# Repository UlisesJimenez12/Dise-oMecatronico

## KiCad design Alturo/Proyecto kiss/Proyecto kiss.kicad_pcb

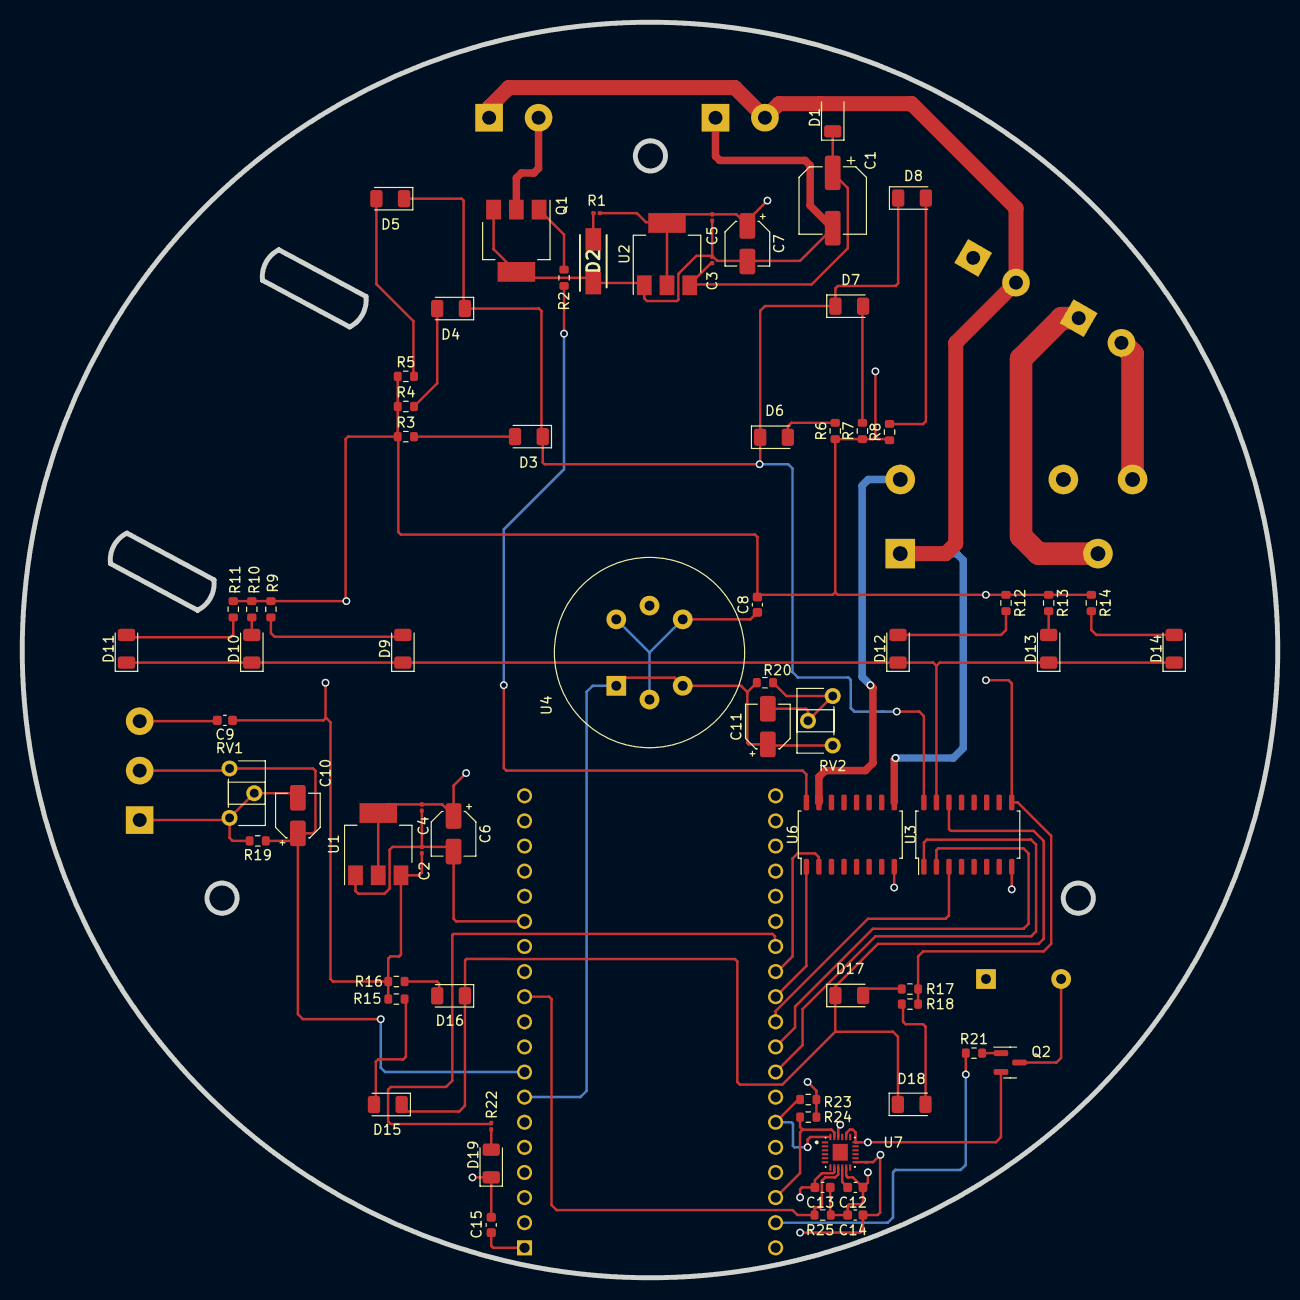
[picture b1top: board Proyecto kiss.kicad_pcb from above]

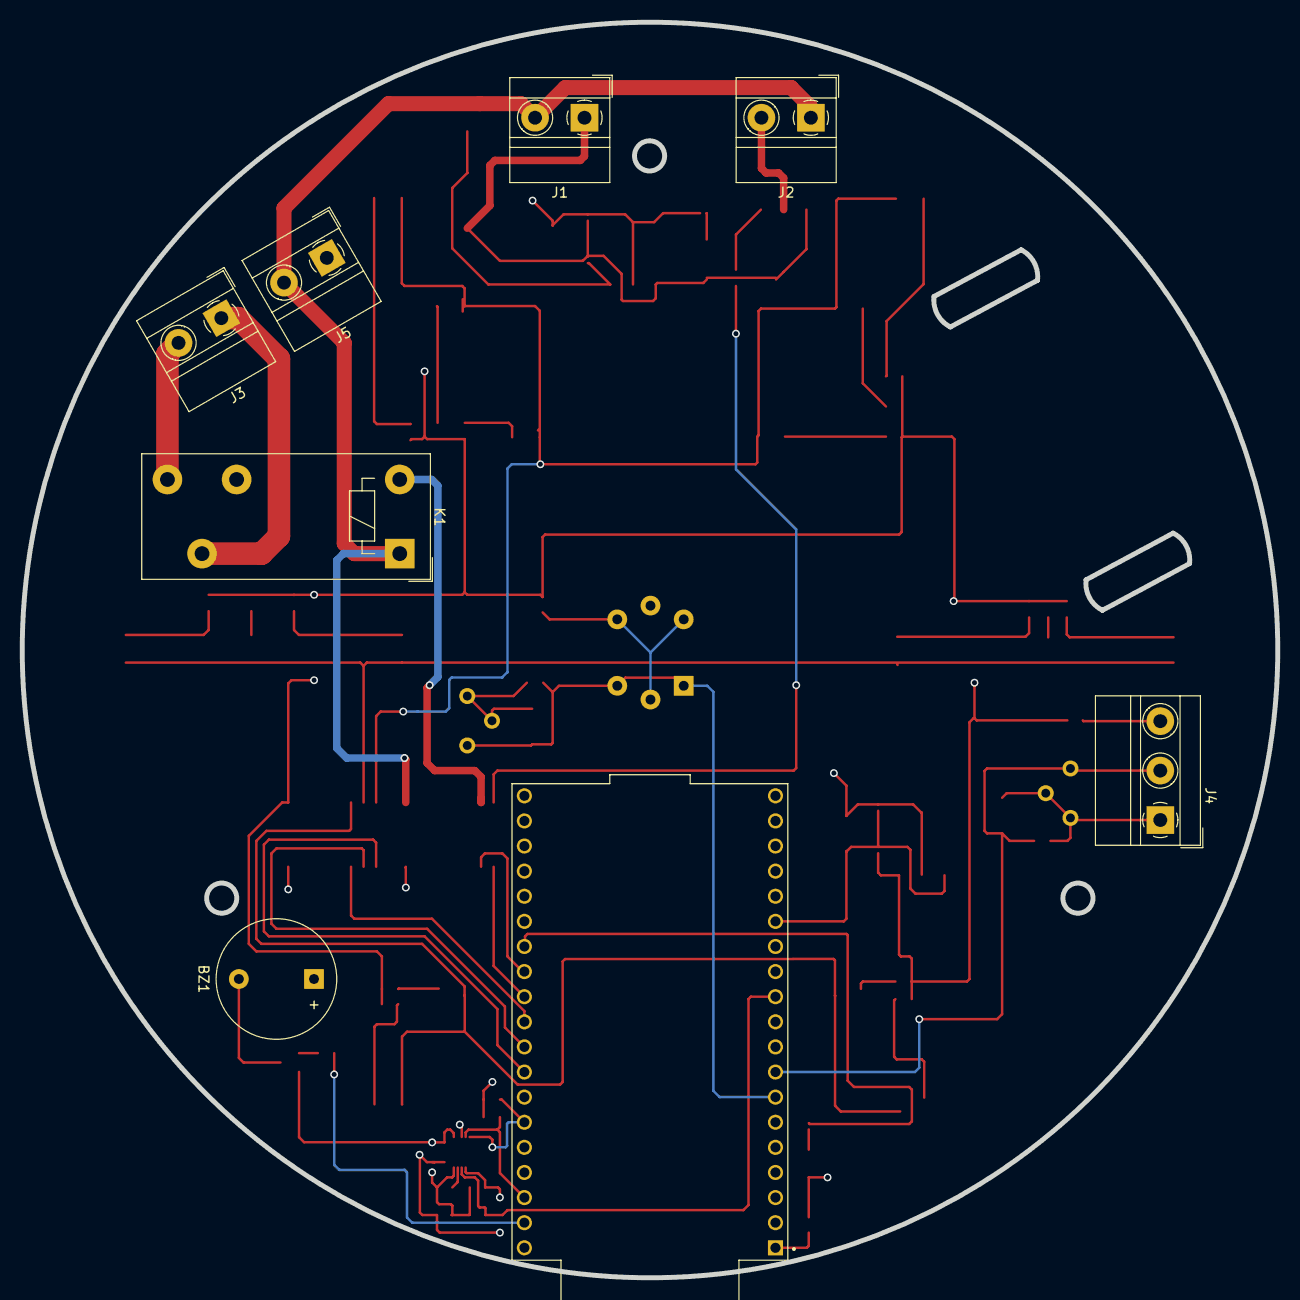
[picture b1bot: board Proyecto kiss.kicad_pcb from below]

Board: 4 copper layers, 127.0 x 127.0 mm, 77 parts (8 on the bottom side), 49 nets.

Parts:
BZ1: Buzzer; Buzzer_12x9.5RM7.6
C1: 100uf; CP_Elec_6.3x5.4
C2, C3, C4, C5: 100nf; C_0201_0603Metric
C6, C7: 22uf; CP_Elec_4x5.4
C8, C9, C12, C14, C15: 100nf; C_0603_1608Metric
C10, C11: 4.7 uF; CP_Elec_4x5.4
C13: 10nF; C_0603_1608Metric
D1: M7; LED_1206_3216Metric
D2: Green_Led; DIOM5327X240N
D3, D4, D5, D6, D7, D8: Red_Led; LED_1206_3216Metric
D9, D10, D11, D12, D13, D14: Blue_Led; LED_1206_3216Metric
D15, D16, D17, D18: Yellow_Led; LED_1206_3216Metric
D19: Green_Led; LED_1206_3216Metric
J1, J2, J3, J5: TB2; TerminalBlock_MetzConnect_Type011_RT05502HBWC_1x02_P5.00mm_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
J4: TB3; TerminalBlock_MetzConnect_Type011_RT05503HBWC_1x03_P5.00mm_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
K1: FINDER-40.31; Relay_SPDT_Finder_40.31
Q1: BSP75N; SOT-223
Q2: BC817; SOT-23
R1, R22: 220; R_0201_0603Metric
R2, R3, R4, R5, R6, R7, R8, R9, R10, R11, R12, R13, R14, R15, R16, R17, R18: 220; R_0603_1608Metric
R19, R20: 100; R_0603_1608Metric
R21: 1K; R_0603_1608Metric
R23, R24, R25: 10k; R_0603_1608Metric
RV1, RV2: 20K; Potentiometer_ACP_CA6-H2,5_Horizontal
U1: AMS1117-3.3; SOT-223-3_TabPin2
U2: AMS1117-5.0; SOT-223-3_TabPin2
U3, U6: ULN2003; SOIC-16_4.55x10.3mm_P1.27mm
U4: MQ-6
U5: ESP32-DEVKITC; MODULE_ESP32-DEVKITC
U7: MPU-6500; QFN40P300X300X95-25N

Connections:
+3.3V: BZ1.1 (-), C4.1, C6.1, C13.2, C14.2, C15.1, U1.2 (VO), U5.1 (3V3), U7.8 (VDDIO), U7.13 (VDD), U7.22 (NCS)
+5V: C2.1, C5.1, C7.1, C8.2, C9.1, R1.1, R3.1, R4.1, R5.1, R6.1, R7.1, R8.1, R9.1, R10.1, R11.1, R12.1, R13.1, R14.1, R15.1, R16.1, R17.1, R18.1, U1.3 (VI), U2.2 (VO), U3.9 (COM)
+12V: D1.2, J1.2, J2.1, J5.2, K1.A1, U6.9 (COM)
/Mod_ESP32/Db_led: R22.1, U5.26 (IO4)
/Mod_Relay/Com: J3.1, K1.11
/Mod_Relay/NO: J3.2, K1.14
/Mod_trans/Trans_out: J2.2, Q1.2 (D)
/Pin_MPU: R25.1, U5.11 (IO27), U7.9 (AD0/SDO)
/Pin_RL: K1.A2, U6.15 (O2)
/Pin_bzz: R21.1, U5.37 (IO23)
/Pin_trans: R2.1, U6.16 (O1)
/SCL: R24.1, U5.36 (IO22), U7.23 (SCL/SCLK)
/SDA: R23.1, U5.33 (IO21), U7.24 (SDA/SDI)
/Sen_ext: C10.1, J4.2, R19.1, RV1.1, U5.8 (IO33)
/Sen_int: C11.1, R20.1, RV2.1, U4.1 (B1), U4.3 (B2), U5.7 (IO32)
/ledB: U3.2 (I2), U5.30 (IO18)
/ledR: U3.1 (I1), U5.31 (IO19)
/ledY: U3.3 (I3), U5.29 (IO5)
Earth: C1.2, C2.2, C3.2, C4.2, C5.2, C6.2, C7.2, C10.2, C11.2, C12.2, C13.1, C14.1, C15.2, D2.1 (K), D19.1 (K), J1.1, J4.1, J5.1, Q1.3 (S), Q1.4 (S), Q2.2 (E), R19.2, R20.2, R23.2, R24.2, R25.2, RV1.2, RV1.3, RV2.2, RV2.3, U1.1 (GND), U2.1 (GND), U3.8 (GND), U4.5 (VH-), U5.14 (GND1), U6.8 (GND), U7.11 (FSYNC), U7.18 (GND), U7.20 (RESV_2)
unnamed: BZ1.2 (+), Q2.3 (C)
unnamed: D2.2 (A), R1.2
unnamed: D3.2 (A), R3.2
unnamed: D3.1 (K), D4.1 (K), D5.1 (K), D6.1 (K), D7.1 (K), D8.1 (K), U3.16 (O1)
unnamed: D4.2 (A), R4.2
unnamed: D5.2 (A), R5.2
unnamed: D6.2 (A), R6.2
unnamed: D7.2 (A), R7.2
unnamed: D8.2 (A), R8.2
unnamed: D9.2 (A), R9.2
unnamed: D10.2 (A), R10.2
unnamed: D9.1 (K), D10.1 (K), D11.1 (K), D12.1 (K), D13.1 (K), D14.1 (K), U3.15 (O2)
unnamed: D11.2 (A), R11.2
unnamed: D12.2 (A), R12.2
unnamed: D13.2 (A), R13.2
unnamed: D14.2 (A), R14.2
unnamed: D15.2 (A), R15.2
unnamed: D15.1 (K), D16.1 (K), D17.1 (K), D18.1 (K), U3.14 (O3)
unnamed: D16.2 (A), R16.2
unnamed: D17.2 (A), R17.2
unnamed: D18.2 (A), R18.2
unnamed: D19.2 (A), R22.2
unnamed: C9.2, J4.3
unnamed: Q1.1 (G), R2.2
unnamed: Q2.1 (B), R21.2
unnamed: C1.1, C3.1, D1.1, U2.3 (VI)
unnamed: C8.1, U4.2 (VH+), U4.4 (A2), U4.6 (A1)
unnamed: U5.27 (IO16), U6.2 (I2)
unnamed: U5.28 (IO17), U6.1 (I1)
unnamed: C12.1, U7.10 (REGOUT)

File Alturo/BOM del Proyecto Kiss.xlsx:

Reference | Value | Footprint | Datasheet | Manufacturer_Part_Number | Mouser Price/Stock | Cdad
BZ1 | Buzzer | Buzzer_Beeper:Buzzer_12x9.5RM7.6 | https://www.mouser.com/datasheet/2/683/IE122303-1-358179.pdf | IE122303-1 | https://www.mouser.com/ProductDetail/DB-Unlimited/IE122303-1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 | 1
C1 | 100uf | Capacitor_SMD:CP_Elec_6.3x5.4 | https://www.mouser.com/datasheet/2/88/AVS-3081846.pdf | AVS107M16D16T-F | https://www.mouser.com/ProductDetail/Cornell-Dubilier-CDE/AV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 | 1
C2-C5, C8, C9, C12, C14, C15 | 100nf | -- valores mixtos -- | https://www.mouser.com/datasheet/2/212/KEM_C1023_X7R_AUTO_SM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 | C0603C104K5RAC3121 | https://www.mouser.com/ProductDetail/KEMET/C0603C104K5RAC312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 | 9
C6, C7 | 22uf | Capacitor_SMD:CP_Elec_4x5.4 | https://www.mouser.com/datasheet/2/212/KEM_A4049_EDH-1102962.pdf | EDH226M016S9BAA | https://www.mouser.com/ProductDetail/KEMET/EDH226M016S9BAA?q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 | 2
C10, C11 | 4.7 uF | Capacitor_SMD:CP_Elec_4x5.4 | https://www.mouser.com/datasheet/2/315/AAB8000C193-947353.pdf | 10SVP4R7M | https://www.mouser.com/ProductDetail/Panasonic/10SVP4R7M?qs=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 | 2
C13 | 10nF | Capacitor_SMD:C_0603_1608Metric | https://www.mouser.com/datasheet/2/396/Taiyo_Yuden_19_MAASL0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 | MAASL063SB7103MFCA01 | https://www.mouser.com/ProductDetail/TAIYO-YUDEN/MAASL063SB7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 | 1
D1 | M7 | M7:DIOM5327X240N | https://www.mouser.in/datasheet/2/849/m1-2577421.pdf | M7 | https://www.mouser.co.uk/ProductDetail/Diotec-Semiconductor/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 | 1
D2 | Green_Led | LED_SMD:LED_1206_3216Metric | https://www.rohm.com/datasheet?p=SML-S13PT&dist=Mouser&media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 | SML-S13PTT68 | https://www.mouser.com/ProductDetail/ROHM-Semiconductor/SML-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 | 1
D3-D8 | Red_Led | LED_SMD:LED_1206_3216Metric | https://www.rohm.com/datasheet?p=SML-S13UT&dist=Mouser&media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 | SML-S13UTT68 | https://www.mouser.com/ProductDetail/ROHM-Semiconductor/SML-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 | 6
D9-D14 | Blue_Led | LED_SMD:LED_1206_3216Metric | https://www.mouser.com/datasheet/2/678/AV02_0977EN_2020_10_2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 | HSMR-C150 | https://www.mouser.com/ProductDetail/Broadcom-Avago/HSMR-C15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 | 6
D15-D18 | Yellow_Led | LED_SMD:LED_1206_3216Metric | https://www.rohm.com/datasheet?p=SML-S13YT&dist=Mouser&media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 | SML-S13YTT68 | https://www.mouser.com/ProductDetail/ROHM-Semiconductor/SML-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 | 4
J1-J3, J5 | TB2 | TerminalBlock_MetzConnect:TerminalBlock_MetzConnect_Type011_RT05502HBWC_1x02_P5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 | https://www.mouser.com/datasheet/2/670/tb002_500-2306853.pdf | TB002-500-02BE | https://www.mouser.com/ProductDetail/CUI-Devices/TB002-500-0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 | 4
J4 | TB3 | TerminalBlock_MetzConnect:TerminalBlock_MetzConnect_Type011_RT05503HBWC_1x03_P5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 | https://www.mouser.com/ProductDetail/Wurth-Elektronik/691101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 | 691101710003 | https://www.mouser.com/datasheet/2/445/691101710003-3089887.pdf | 1
K1 | FINDER-40.31 | Relay_THT:Relay_SPDT_Finder_40.31 | http://gfinder.findernet.com/assets/Series/353/S40EN.pdf | 40.31.8.230.0000 | https://us.rs-online.com/product/finder/40-31-8-230-0000/70747659/ | 1
Q1 | BSP75N | Package_TO_SOT_SMD:SOT-223 | https://www.infineon.com/dgdl/Infineon-BSP75N-DS-v01_04-en.p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 | BSP75N | https://www.mouser.com/ProductDetail/Infineon-Technologies/B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 | 1
Q2 | BC817 | Package_TO_SOT_SMD:SOT-23 | https://www.mouser.com/datasheet/2/345/bc817-2449263.pdf | BC817 | https://www.mouser.com/ProductDetail/Rectron/BC817?qs=sGAEpi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 | 1
R1-R18 | 220 | -- valores mixtos -- | https://www.mouser.com/datasheet/2/427/crcw0201e3-1761851.pdf | CRCW0201220KFKED | https://www.mouser.com/ProductDetail/Vishay-Dale/CRCW0201220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 | 18
R19, R20 | 100 | Resistor_SMD:R_0603_1608Metric | https://www.mouser.com/datasheet/2/315/PANA_S_A0013004771_1-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 | ERA-1AEB101C | https://www.mouser.com/ProductDetail/Panasonic/ERA-1AEB101C?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 | 2
R21 | 1K | Resistor_SMD:R_0603_1608Metric | https://www.mouser.com/datasheet/2/418/8/ENG_DS_1773200_N2-2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 | CPF0201B1K0E1 | https://www.mouser.com/ProductDetail/TE-Connectivity-Holswor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 | 1
RV1, RV2 | 20K | Potentiometer_THT:Potentiometer_ACP_CA6-H2,5_Horizontal | https://www.mouser.com/datasheet/2/670/ptn06-3075547.pdf | PTN06-B20CC20 | https://www.mouser.com/ProductDetail/CUI-Devices/PTN06-B20CC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 | 2
U1 | AMS1117-3.3 | Package_TO_SOT_SMD:SOT-223-3_TabPin2 | https://www.ti.com/general/docs/suppproductinfo.tsp?distId=2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 | REG1117-3.3 | https://www.mouser.com/ProductDetail/Texas-Instruments/REG11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 | 1
U2 | AMS1117-5.0 | Package_TO_SOT_SMD:SOT-223-3_TabPin2 | https://www.ti.com/general/docs/suppproductinfo.tsp?distId=2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 | REG1117-5 | https://www.mouser.com/ProductDetail/Texas-Instruments/REG11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 | 1
U3, U6 | ULN2003 | Package_SO:SOIC-16_4.55x10.3mm_P1.27mm | http://www.ti.com/lit/ds/symlink/uln2003a.pdf | ULN2004AD | https://www.mouser.com/ProductDetail/Texas-Instruments/ULN20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 | 2
U4 | MQ-6 | Sensor:MQ-6 | https://www.winsen-sensor.com/d/files/semiconductor/mq-6.pdf | MQ-6 | https://www.ebay.com/itm/191834810651?hash=item2caa3ee91b:g: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 | 1
U5 | ESP32-DEVKITC | esp32:MODULE_ESP32-DEVKITC | https://esp-idf.readthedocs.io/en/latest/get-started/get-sta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 | ESP32-DevKitC | https://www.mouser.com/ProductDetail/Espressif-Systems/ESP32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 | 1
U7 | MPU-6500 | MPU-6500:QFN40P300X300X95-25N | https://product.tdk.com/system/files/dam/doc/product/sensor/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 | MPU-6500 | https://www.mouser.com/ProductDetail/TDK-InvenSense/MPU-6500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 | 1

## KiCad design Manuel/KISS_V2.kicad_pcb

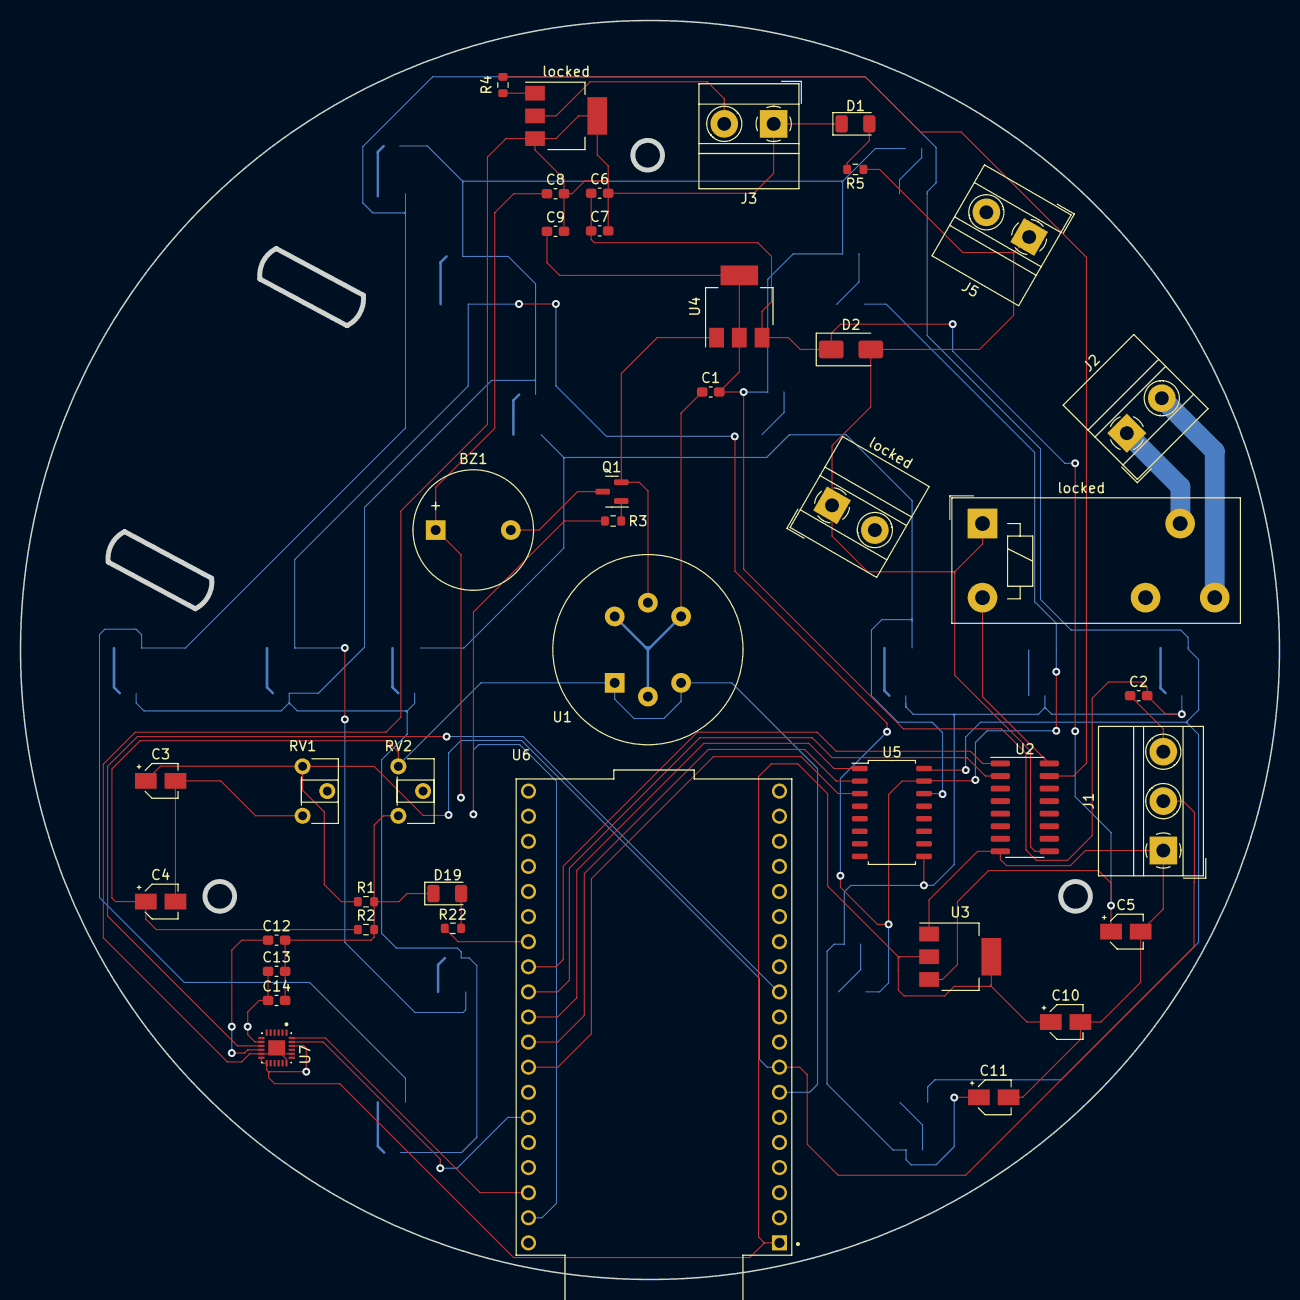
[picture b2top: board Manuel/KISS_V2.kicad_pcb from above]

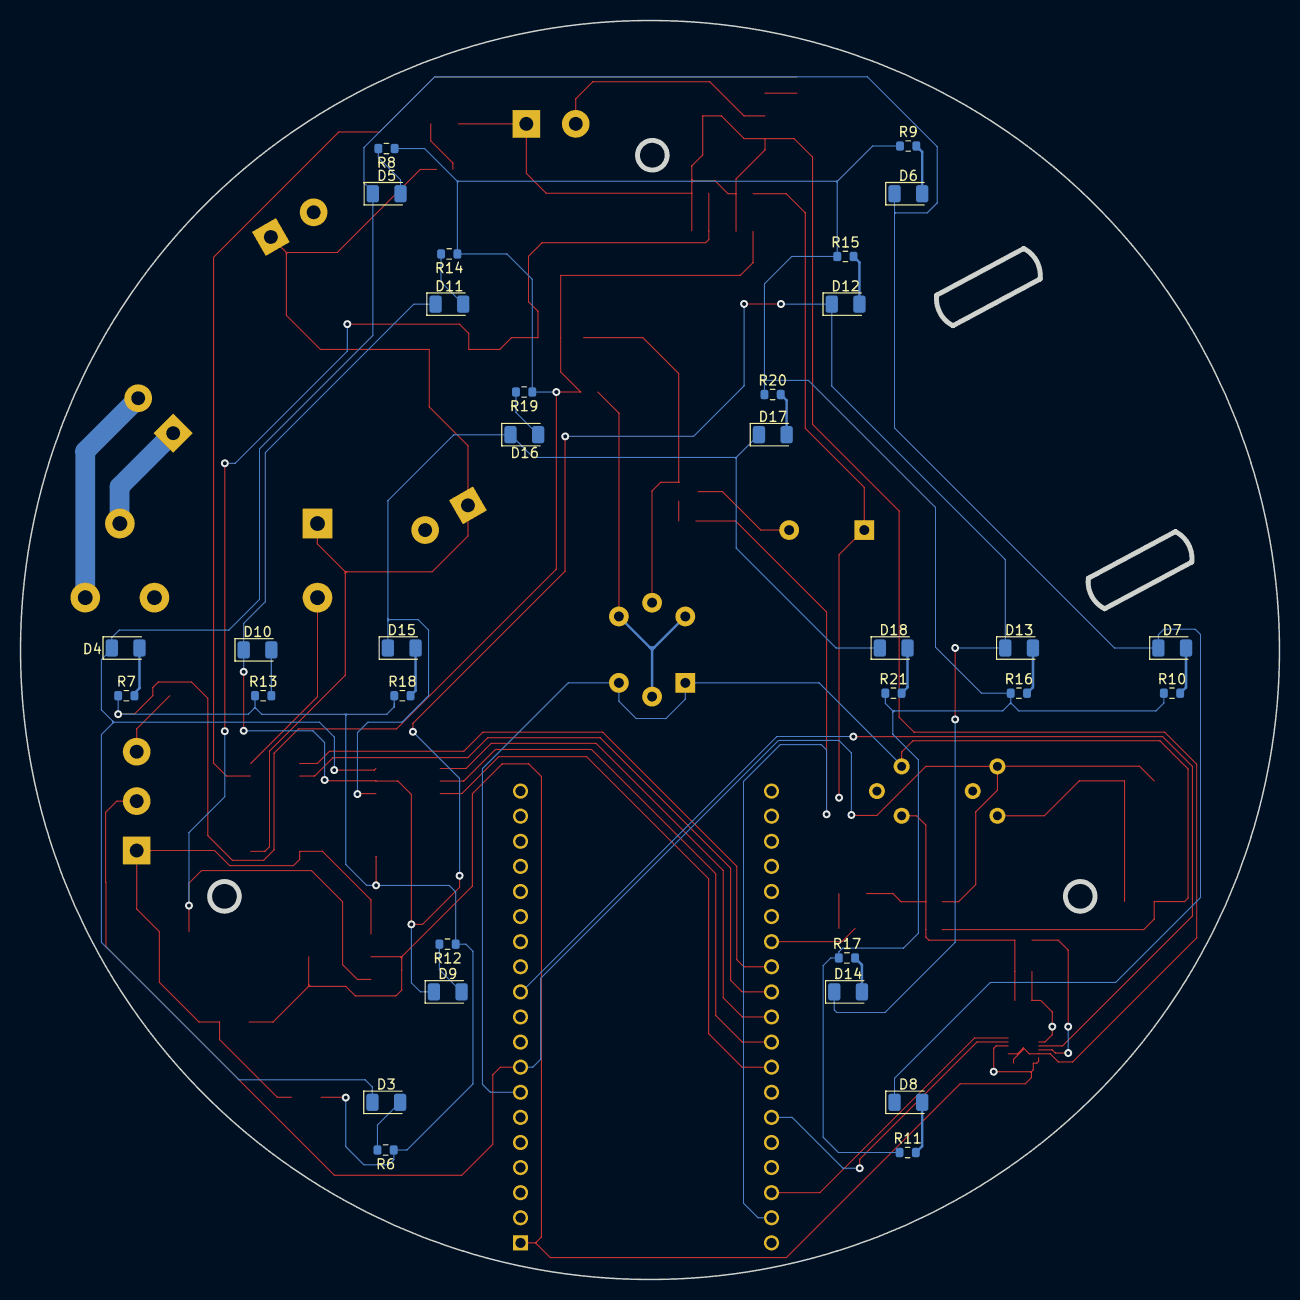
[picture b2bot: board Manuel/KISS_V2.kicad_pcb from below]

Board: 4 copper layers, 127.4 x 127.4 mm, 73 parts (32 on the bottom side), 49 nets.

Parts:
BZ1: Buzzer; Buzzer_12x9.5RM7.6
C1, C2: 100nF; C_0603_1608Metric_Pad1.08x0.95mm_HandSolder
C3, C4: 4.7 uF; CP_Elec_3x5.3
C5: 100uf; CP_Elec_3x5.3
C6, C7, C8, C9: 100nf; C_0603_1608Metric_Pad1.08x0.95mm_HandSolder
C10, C11: 22uf; CP_Elec_3x5.3
C12, C14: 0.1μF; C_0603_1608Metric_Pad1.08x0.95mm_HandSolder
C13: 10nF; C_0603_1608Metric_Pad1.08x0.95mm_HandSolder
D1, D3, D4, D5, D7, D8, D9, D10, D11, D12, D13, D14, D15, D16, D17, D18, D19: LED; LED_1206_3216Metric
D2: M1; D_SMA
D6: locked; LED_1206_3216Metric
J1: Screw_Terminal_01x03; TerminalBlock_MetzConnect_Type011_RT05503HBWC_1x03_P5.00mm_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
J2, J3, J5: Screw_Terminal_01x02; TerminalBlock_MetzConnect_Type011_RT05502HBWC_1x02_P5.00mm_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
Q1: BC817; SOT-23
R1, R2: 100; R_0603_1608Metric
R3: 1K; R_0603_1608Metric
R4, R5, R6, R7, R8, R9, R10, R11, R12, R13, R14, R15, R16, R17, R18, R19, R20, R21, R22: 220; R_0603_1608Metric
RV1, RV2: 20K; Potentiometer_ACP_CA6-H2,5_Horizontal
U1: MQ-6
U2: ULN2003; SOIC-16_3.9x9.9mm_P1.27mm
U3: AMS1117-3.3; SOT-223-3_TabPin2
U4: AMS1117-5.0; SOT-223-3_TabPin2
U5: ULN2003; SOIC-16_4.55x10.3mm_P1.27mm
U6: ESP32-DEVKITC; MODULE_ESP32-DEVKITC
U7: MPU-6500; QFN40P300X300X95-25N
locked: Screw_Terminal_01x02; TerminalBlock_MetzConnect_Type011_RT05502HBWC_1x02_P5.00mm_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
locked#2: locked; SOT-223
locked#3: locked; Relay_SPDT_Finder_40.31

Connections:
3.3V: BZ1.1 (-), C8.1, C10.1, C13.1, C14.1, U3.2 (VO), U6.1 (3V3), U7.8 (VDDIO), U7.12 (INT), U7.13 (VDD), U7.22 (NCS)
5V: C1.2, C2.1, C9.1, C11.1, R6.1, R7.1, R8.1, R9.1, R10.1, R11.1, R12.1, R13.1, R14.1, R15.1, R16.1, R17.1, R18.1, R19.1, R20.1, R21.1, U4.2 (VO), U5.9 (COM)
/Buzzer/Activador del buzzer: R3.1, U6.37 (IO23)
/Controlador/COM: J2.1, locked#3.11
/Controlador/Modulo de Diodos/D1: U2.16 (O1), locked#3.A2
/Controlador/Modulo de Diodos/EN_D1: U2.1 (I1), U6.27 (IO16)
/Controlador/Modulo de Diodos/EN_D2: U2.2 (I2), U6.28 (IO17)
/Controlador/NA_RL: J2.2, locked#3.14
/Controlador/Pin_Activador_LEDam: U5.1 (I1), U6.29 (IO5)
/Controlador/Pin_Activador_LEDaz: U5.2 (I2), U6.30 (IO18)
/Controlador/Pin_Activador_LEDr: U5.3 (I3), U6.31 (IO19)
/Controlador/Pin_Sensor_Gas: C4.1, R2.1, RV2.1, U1.1 (B1), U1.3 (B2), U6.7 (IO32)
/Controlador/Pin_Sensor_GasEx: C3.1, J1.2, R1.1, RV1.1, U6.8 (IO33)
/Controlador/SALIDA TRANSISTOR: J3.2, locked#2.2 (D)
/Controlador/SCL: U6.36 (IO22), U7.24 (SDA/SDI)
/Controlador/SDA: U6.33 (IO21), U7.23 (SCL/SCLK)
/Controlador/Salida_Giroscopio: U6.11 (IO27), U7.9 (AD0/SDO)
Activador de transistor: R4.1, U2.15 (O2)
Earth: C3.2, C4.2, C5.2, C6.2, C7.2, C8.2, C9.2, C10.2, C11.2, C12.2, C13.2, C14.2, D1.1 (K), D19.1 (K), J1.1, J3.1, J5.2, Q1.2 (E), R1.2, R2.2, RV1.2, RV1.3, RV2.2, RV2.3, U1.5 (VH-), U2.8 (GND), U3.1 (GND), U4.1 (GND), U6.14 (GND1), U7.11 (FSYNC), U7.18 (GND), U7.20 (RESV_2), U7.25 (EXP), locked.2, locked#2.3 (S), locked#2.4 (S)
unnamed: BZ1.2 (+), Q1.3 (C)
unnamed: D1.2 (A), R5.2
unnamed: C5.1, C6.1, C7.1, D2.1 (K), U3.3 (VI), U4.3 (VI)
unnamed: D3.2 (A), R6.2
unnamed: D3.1 (K), D4.1 (K), D5.1 (K), D6.1 (K), D7.1 (K), D8.1 (K), U5.16 (O1)
unnamed: D4.2 (A), R7.2
unnamed: D5.2 (A), R8.2
unnamed: D6.2 (A), R9.2
unnamed: D7.2 (A), R10.2
unnamed: D8.2 (A), R11.2
unnamed: D9.2 (A), R12.2
unnamed: D10.2 (A), R13.2
unnamed: D9.1 (K), D10.1 (K), D11.1 (K), D12.1 (K), D13.1 (K), D14.1 (K), U5.15 (O2)
unnamed: D11.2 (A), R14.2
unnamed: D12.2 (A), R15.2
unnamed: D13.2 (A), R16.2
unnamed: D14.2 (A), R17.2
unnamed: D15.2 (A), R18.2
unnamed: D15.1 (K), D16.1 (K), D17.1 (K), D18.1 (K), U5.14 (O3)
unnamed: D16.2 (A), R19.2
unnamed: D17.2 (A), R20.2
unnamed: D18.2 (A), R21.2
unnamed: D19.2 (A), R22.2
unnamed: C2.2, J1.3
unnamed: Q1.1 (B), R3.2
unnamed: R4.2, locked#2.1 (G)
unnamed: C1.1, U1.2 (VH+), U1.4 (A2), U1.6 (A1)
unnamed: R22.1, U6.26 (IO4)
unnamed: C12.1, U7.10 (REGOUT)
Positivo de bateria: D2.2 (A), J5.1, R5.1, U2.9 (COM), locked.1, locked#3.A1

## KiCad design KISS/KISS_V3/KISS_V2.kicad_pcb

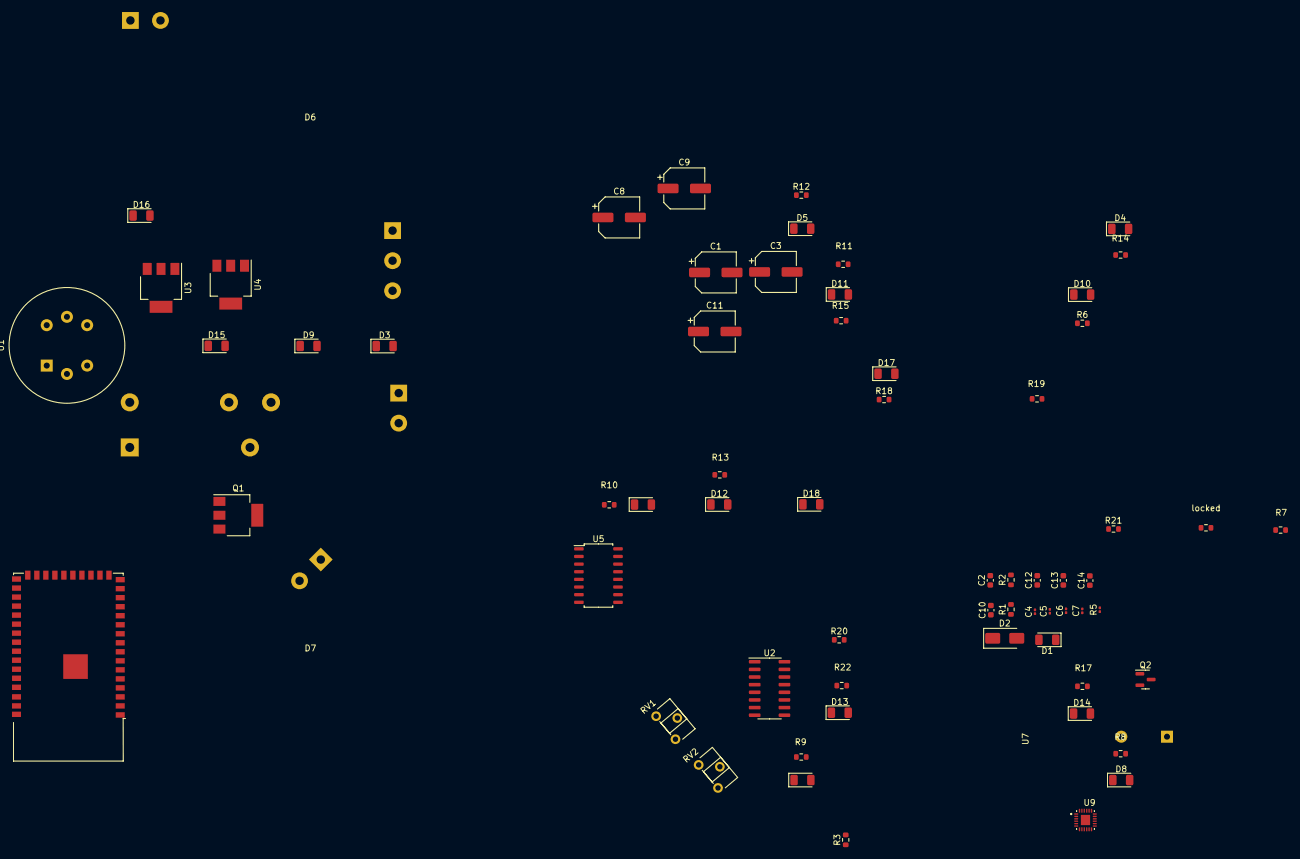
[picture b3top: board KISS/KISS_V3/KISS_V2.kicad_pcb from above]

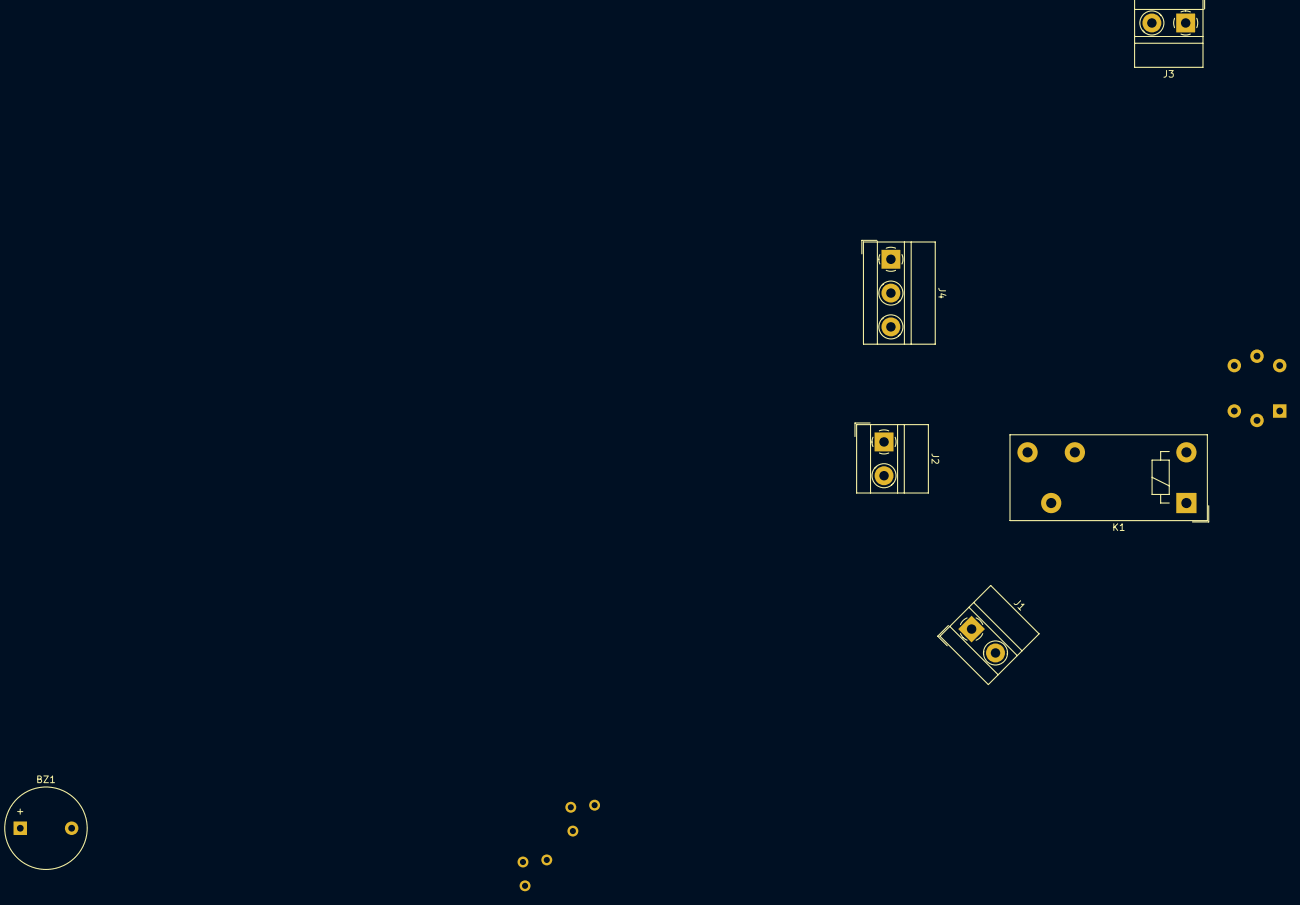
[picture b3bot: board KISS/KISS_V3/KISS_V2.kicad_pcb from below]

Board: 2 copper layers, 70 parts (6 on the bottom side), 48 nets, no tracks yet.

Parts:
BZ1: Buzzer; Buzzer_12x9.5RM7.6
C1, C11: 4.7 uF; CP_Elec_6.3x7.7
C2, C10: C; C_0603_1608Metric
C3: 100uf; CP_Elec_6.3x3
C4, C5, C6, C7: 100nf; C_0201_0603Metric
C8, C9: 22uf; CP_Elec_6.3x3
C12, C13: 0.1μF; C_0603_1608Metric
C14: 10nF; C_0603_1608Metric
D1, D3, D4, D5, D6, D7, D8, D9, D10, D11, D12, D13, D14, D15, D16, D17, D18: LED; LED_1206_3216Metric
D2: M1; D_SMA
J1, J2, J3: Screw_Terminal_01x02; TerminalBlock_MetzConnect_Type011_RT05502HBWC_1x02_P5.00mm_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
J4: Screw_Terminal_01x03; TerminalBlock_MetzConnect_Type011_RT05503HBWC_1x03_P5.00mm_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
K1: FINDER-40.31; Relay_SPDT_Finder_40.31
Q1: BSP75N; SOT-223
Q2: BC817; SOT-23
R1, R2: 100; R_0603_1608Metric
R3: 1K; R_0603_1608Metric
R5: 220; R_0201_0603Metric
R6, R7, R8, R9, R10, R11, R12, R13, R14, R15, R17, R18, R19, R20, R21, R22: 220; R_0603_1608Metric
RV1, RV2: 60K; Potentiometer_ACP_CA6-H2,5_Horizontal
U1: MQ-6
U2: ULN2003; SOIC-16_3.9x9.9mm_P1.27mm
U3: AMS1117-3.3; SOT-223-3_TabPin2
U4: AMS1117-5.0; SOT-223-3_TabPin2
U5: ULN2003; SOIC-16_4.55x10.3mm_P1.27mm
U7: ESP32-S2-WROVER-I; ESP32-S2-WROVER
U9: MPU-6500; QFN40P300X300X95-25N
locked: 220; R_0603_1608Metric

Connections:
3.3V: BZ1.1 (-), C6.1, C8.1, C12.2, C14.2, U3.2 (VO), U7.2 (3V3), U9.8 (VDDIO), U9.12 (INT), U9.13 (VDD), U9.22 (NCS)
5V: C2.2, C7.1, C9.1, C10.1, R6.1, R7.1, R8.1, R9.1, R10.1, R11.1, R12.1, R13.1, R14.1, R15.1, R17.1, R18.1, R19.1, R21.1, R22.1, U4.2 (VO), locked.1
/Buzzer/Activador del buzzer: R3.1, U7.39 (IO45)
/Controlador/INPUT_RL: J2.1, K1.11
/Controlador/Modulo de Diodos/D1: K1.A2, U2.16 (O1)
/Controlador/Modulo de Diodos/EN_D1: U2.1 (I1), U7.25 (IO26)
/Controlador/Modulo de Diodos/EN_D2: U2.2 (I2), U7.27 (IO33)
/Controlador/OUT_RL: J2.2, K1.14
/Controlador/Pin_Activador_LEDam: U5.2 (I2), U7.30 (IO36)
/Controlador/Pin_Activador_LEDaz: U5.3 (I3), U7.31 (IO37)
/Controlador/Pin_Activador_LEDr: U5.1 (I1), U7.32 (IO38)
/Controlador/Pin_Sensor_Gas: C1.1, R2.1, RV1.1, U1.1 (B1), U1.3 (B2), U7.4 (IO01)
/Controlador/Pin_Sensor_GasEx: C11.1, J4.2, R1.1, RV2.1, U7.5 (IO02)
/Controlador/SALIDA TRANSISTOR: J3.2, Q1.2 (D)
/Controlador/SCL: U7.12 (IO09), U9.24 (SDA/SDI)
/Controlador/SDA: U7.11 (IO08), U9.23 (SCL/SCLK)
Activador de transistor: R20.1, U2.15 (O2)
Earth: C1.2, C3.2, C4.2, C5.2, C6.2, C7.2, C8.2, C9.2, C11.2, C12.1, C13.2, C14.1, D1.1 (K), J1.2, J4.1, Q1.3 (S), Q1.4 (S), Q2.2 (E), R1.2, R2.2, RV1.2, RV1.3, RV2.2, RV2.3, U1.5 (VH-), U2.8 (GND), U3.1 (GND), U4.1 (GND), U7.1 (GND), U7.26 (GND), U7.42 (GND), U7.43 (GND), U9.11 (FSYNC), U9.18 (GND), U9.20 (RESV_2)
GNDREF: U5.8 (GND), U5.9 (COM)
unnamed: BZ1.2 (+), Q2.3 (C)
unnamed: D1.2 (A), R5.2
unnamed: C3.1, C4.1, C5.1, D2.1 (K), U3.3 (VI), U4.3 (VI)
unnamed: D3.2 (A), R19.2
unnamed: D3.1 (K), D4.1 (K), D5.1 (K), D6.1 (K), D7.1 (K), D8.1 (K), U5.16 (O1)
unnamed: D4.2 (A), R14.2
unnamed: D5.2 (A), R12.2
unnamed: D6.2 (A), R10.2
unnamed: D7.2 (A), R8.2
unnamed: D8.2 (A), R6.2
unnamed: D9.2 (A), R7.2
unnamed: D10.2 (A), R9.2
unnamed: D11.2 (A), R11.2
unnamed: D12.2 (A), R13.2
unnamed: D13.2 (A), R15.2
unnamed: D14.2 (A), R17.2
unnamed: D15.2 (A), locked.2
unnamed: D16.2 (A), R18.2
unnamed: D17.2 (A), R21.2
unnamed: D18.2 (A), R22.2
unnamed: C10.2, J4.3
unnamed: Q1.1 (G), R20.2
unnamed: Q2.1 (B), R3.2
unnamed: C2.1, U1.2 (VH+), U1.4 (A2), U1.6 (A1)
unnamed: C13.1, U9.10 (REGOUT)
Positivo de Baateria: D2.2 (A), R5.1
Positivo de bateria: J1.1, K1.A1, U2.9 (COM)
Tira 2: D9.1 (K), D10.1 (K), D11.1 (K), D12.1 (K), D13.1 (K), D14.1 (K), U5.15 (O2)
Tira 3: D15.1 (K), D16.1 (K), D17.1 (K), D18.1 (K), U5.14 (O3)

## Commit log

2023-02-05 Se agrega el documento
2023-03-31 Agregando todas las versiones actuales
2023-03-31 Agregado de carpetas
2023-03-31 Creacion de carpetas
2023-03-31 Creacion carpeta pichardo
2023-04-01 Create lol
2023-04-01 Create prueba1
2023-04-01 Create fp-info-cache
2023-04-01 Proyecto Kiss V2
    Esquemático corregidó y PCB organizado sin enrutar
2023-04-02 Create #auto_saved_files#
2023-04-02 Proyecto Kiss V2
    Esquemático y PCB terminados
2023-04-04 PCB
    PCB corregido
2023-04-04 PCB
    Correcion de las capas del medio
2023-04-24 piezas para impresion
